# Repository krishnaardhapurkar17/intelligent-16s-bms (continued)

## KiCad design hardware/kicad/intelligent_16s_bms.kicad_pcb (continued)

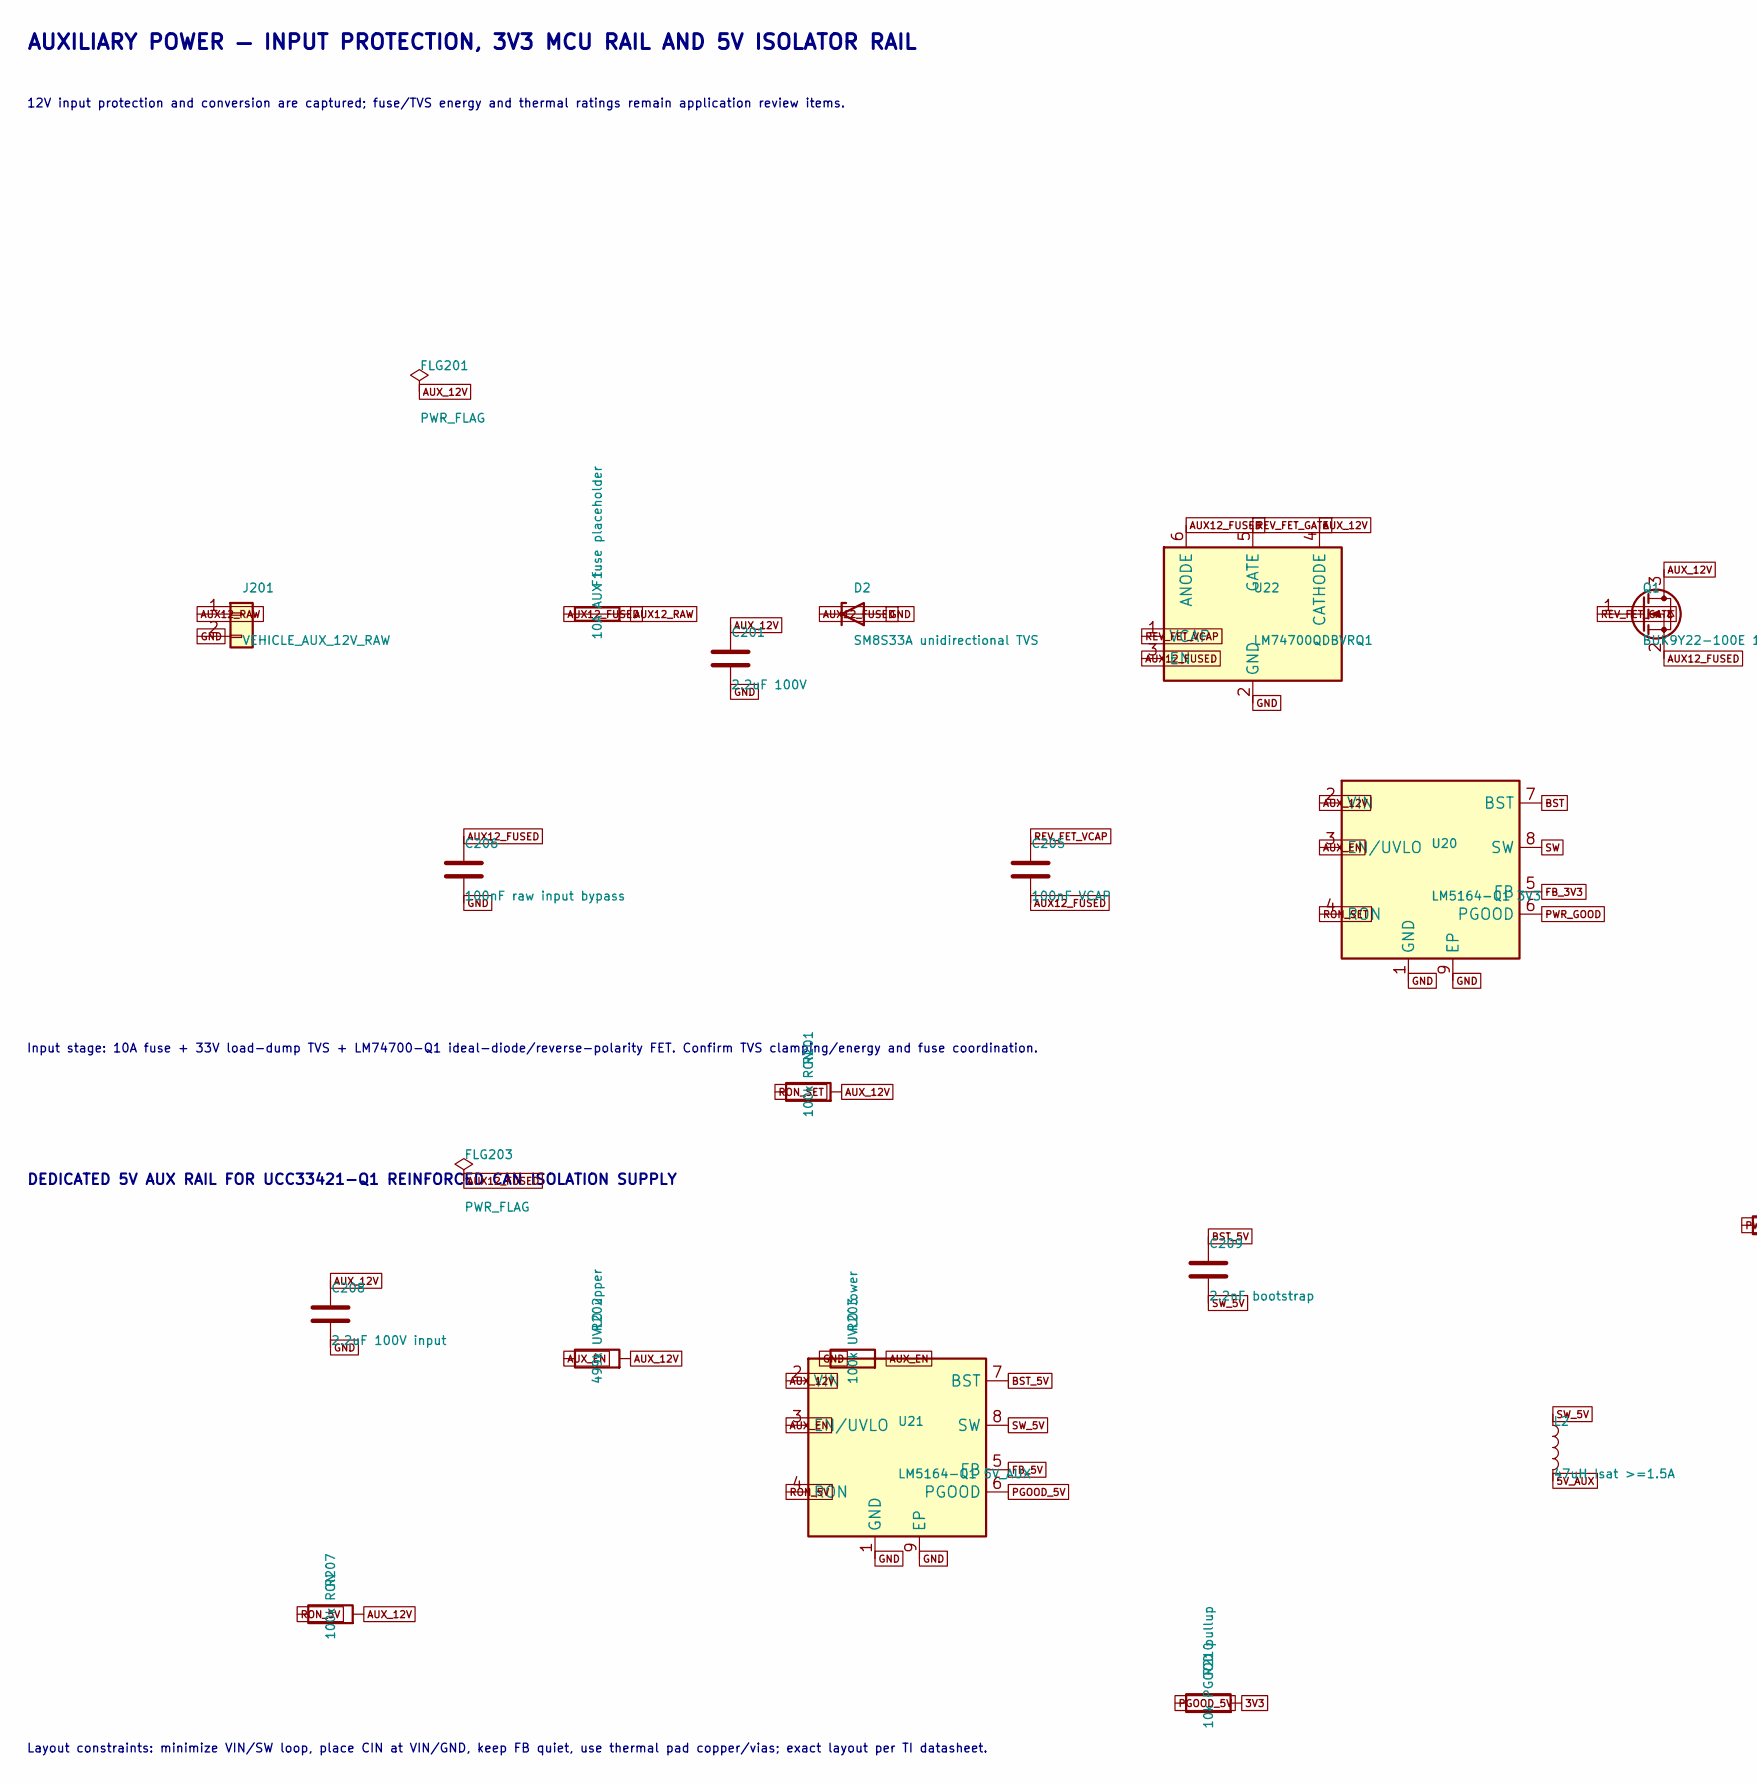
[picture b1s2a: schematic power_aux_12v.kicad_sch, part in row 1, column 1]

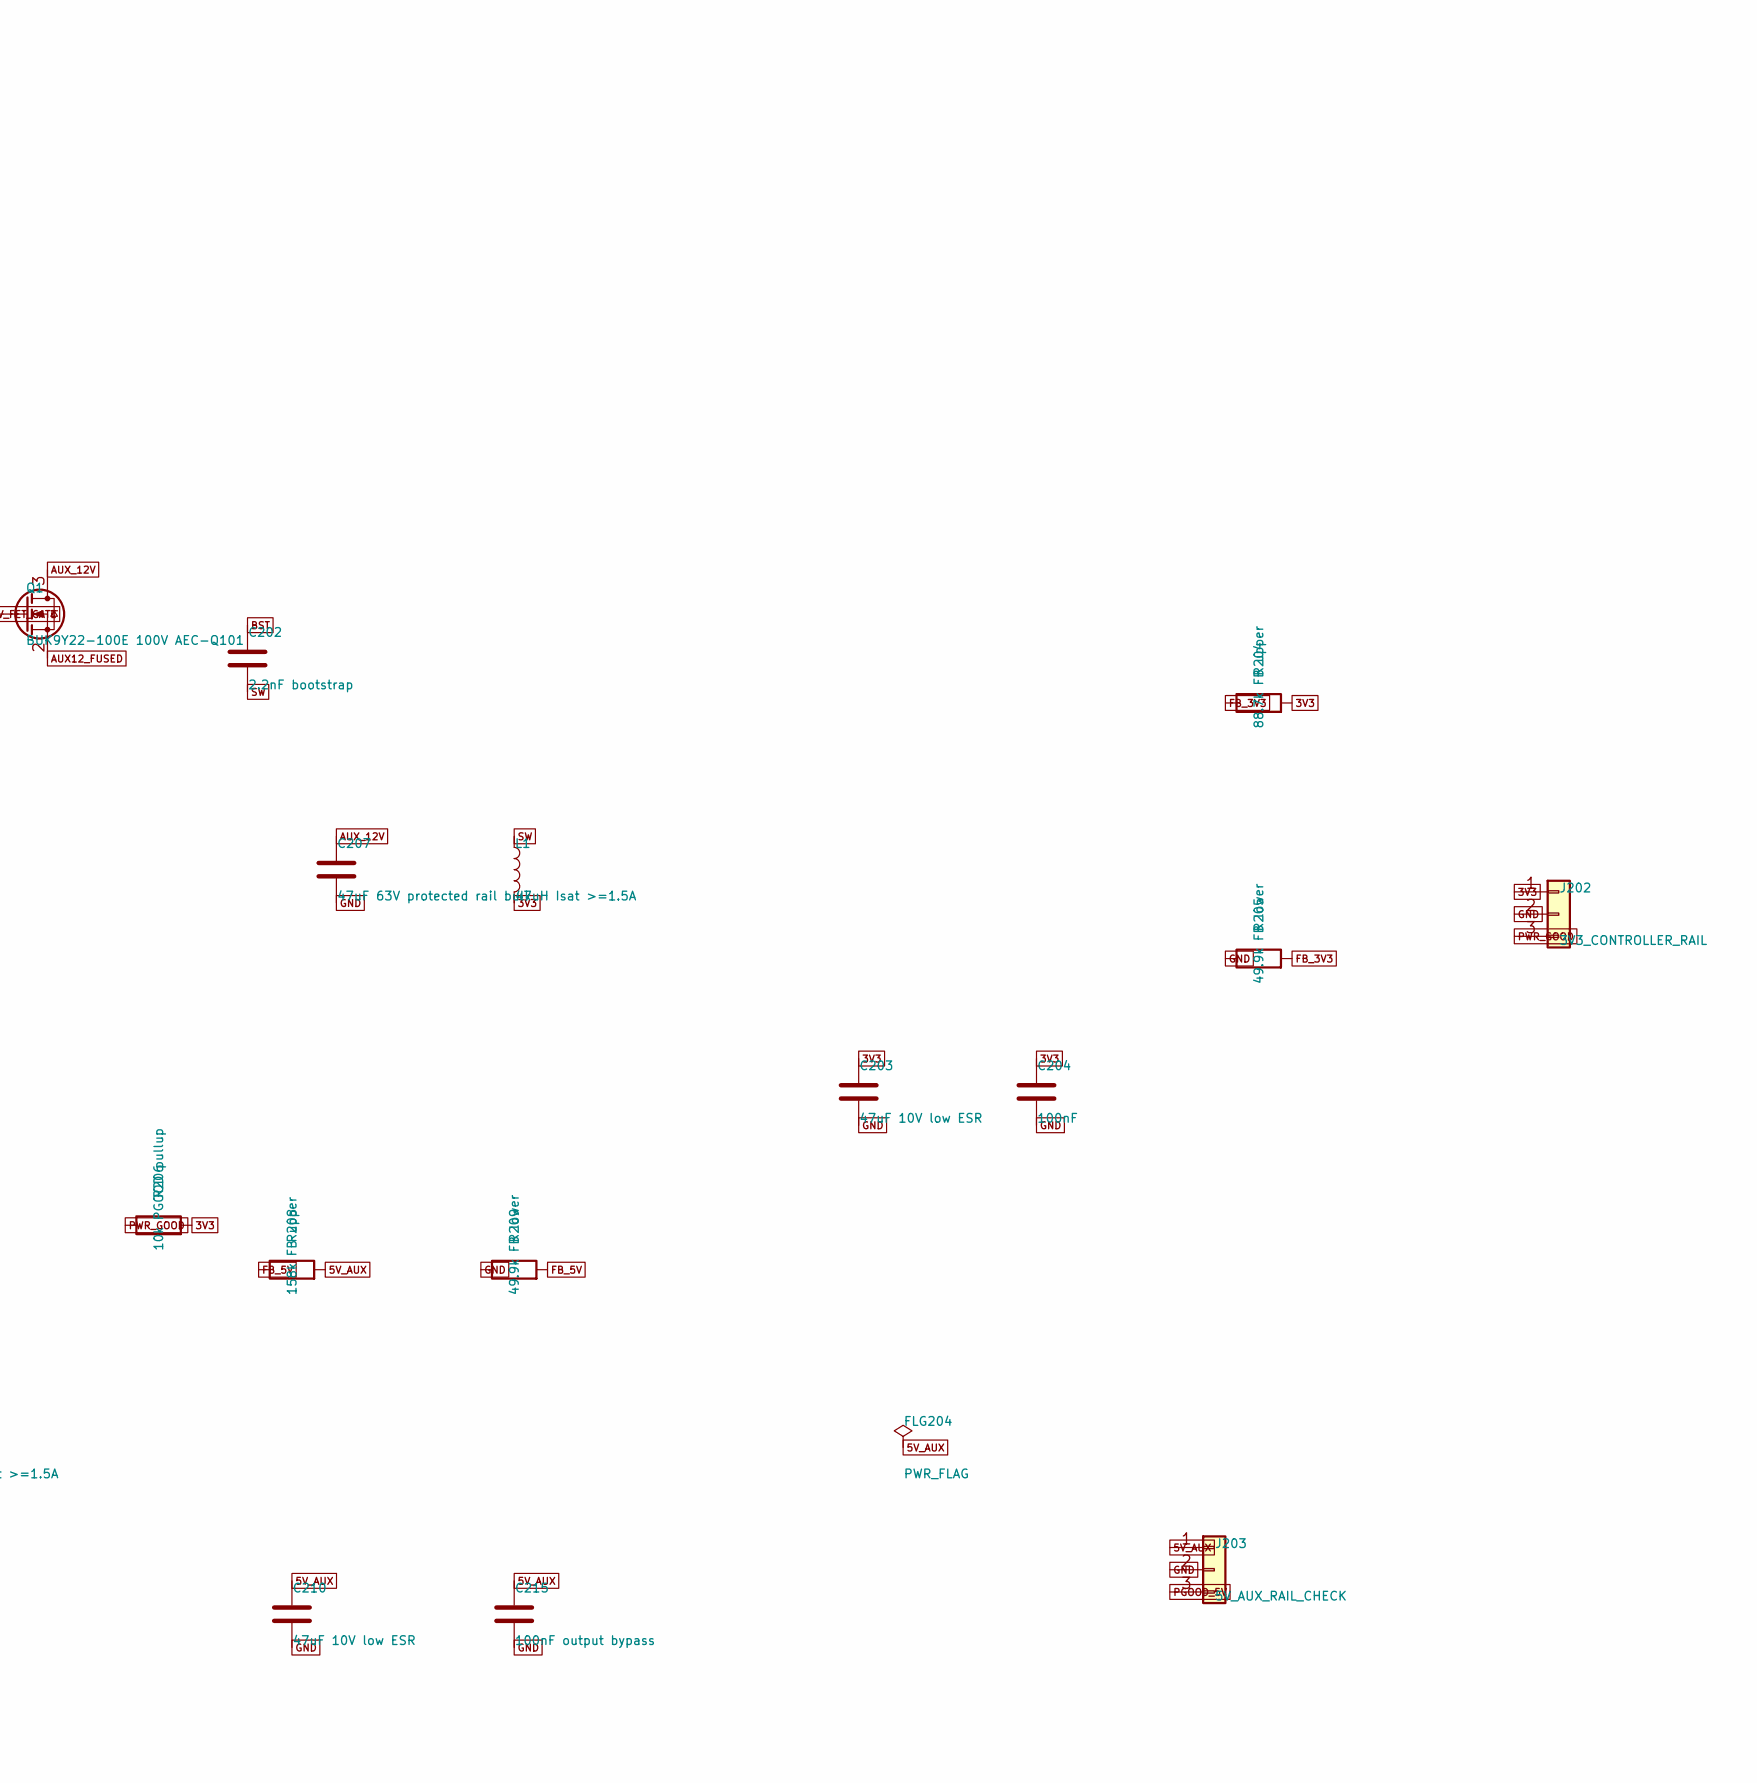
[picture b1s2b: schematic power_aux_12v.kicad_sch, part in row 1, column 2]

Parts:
C201: 2.2uF 100V; C_1210_3225Metric
C202, C209: 2.2nF bootstrap; C_0603_1608Metric
C203, C210: 47uF 10V low ESR; C_1210_3225Metric
C204: 100nF; C_0603_1608Metric
C205: 100nF VCAP; C_0603_1608Metric
C206: 100nF raw input bypass; C_0603_1608Metric
C207: 47uF 63V protected rail bulk; C_1210_3225Metric
C208: 2.2uF 100V input; C_1210_3225Metric
C215: 100nF output bypass; C_0603_1608Metric
D2: SM8S33A unidirectional TVS
F1: 10A AUX fuse placeholder
FLG201, FLG203, FLG204: PWR_FLAG
J201: VEHICLE_AUX_12V_RAW; TerminalBlock_Phoenix_MKDS-1,5-2-5.08_1x02_P5.08mm_Horizont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
J202: 3V3_CONTROLLER_RAIL; PinHeader_1x03_P2.54mm_Vertical
J203: 5V_AUX_RAIL_CHECK; PinHeader_1x03_P2.54mm_Vertical
L1, L2: 47uH Isat >=1.5A; L_12x12mm_H6mm
Q1: BUK9Y22-100E 100V AEC-Q101; LFPAK56
R201, R207: 100k RON; R_0603_1608Metric
R202: 499k UVLO upper; R_0603_1608Metric
R203: 100k UVLO lower; R_0603_1608Metric
R204: 88.7k FB upper; R_0603_1608Metric
R205, R209: 49.9k FB lower; R_0603_1608Metric
R206, R210: 10k PGOOD pullup; R_0603_1608Metric
R208: 158k FB upper; R_0603_1608Metric
U20: LM5164-Q1 3V3; TI_SO-PowerPAD-8
U21: LM5164-Q1 5V_AUX; TI_SO-PowerPAD-8
U22: LM74700QDBVRQ1; SOT-23-6

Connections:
3V3: C203.1, C204.1, J202.1, L1.2, R204.2, R206.2, R210.2; also elsewhere on the board
5V_AUX: C210.1, C215.1, FLG204.1, J203.1, L2.2, R208.2; also elsewhere on the board
AUX12_FUSED: C205.2, C206.1, D2.1 (K), F1.1, FLG203.1, Q1.2 (S), U22.3 (EN), U22.6 (ANODE)
AUX12_RAW: F1.2, J201.1
AUX_12V: C201.1, C207.1, C208.1, FLG201.1, Q1.3 (D), R201.2, R202.2, R207.2, U20.2 (VIN), U21.2 (VIN), U22.4 (CATHODE); also elsewhere on the board
AUX_EN: R202.1, R203.2, U20.3 (EN/UVLO), U21.3 (EN/UVLO)
BST: C202.1, U20.7 (BST)
BST_5V: C209.1, U21.7 (BST)
FB_3V3: R204.1, R205.2, U20.5 (FB)
FB_5V: R208.1, R209.2, U21.5 (FB)
GND: C201.2, C203.2, C204.2, C206.2, C207.2, C208.2, C210.2, C215.2, D2.2 (A), J201.2, J202.2, J203.2, R203.1, R205.1, R209.1, U20.1 (GND), U20.9 (EP), U21.1 (GND), U21.9 (EP), U22.2 (GND); also elsewhere on the board
PGOOD_5V: J203.3, R210.1, U21.6 (PGOOD)
PWR_GOOD: J202.3, R206.1, U20.6 (PGOOD)
REV_FET_GATE: Q1.1 (G), U22.5 (GATE)
REV_FET_VCAP: C205.1, U22.1 (VCAP)
RON_5V: R207.1, U21.4 (RON)
RON_SET: R201.1, U20.4 (RON)
SW: C202.2, L1.1, U20.8 (SW)
SW_5V: C209.2, L2.1, U21.8 (SW)

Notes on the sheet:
Layout constraints: minimize VIN/SW loop, place CIN at VIN/GND, keep FB quiet, use thermal pad copper/vias; exact layout per TI datasheet.
12V input protection and conversion are captured; fuse/TVS energy and thermal ratings remain application review items.
DEDICATED 5V AUX RAIL FOR UCC33421-Q1 REINFORCED CAN ISOLATION SUPPLY
AUXILIARY POWER — INPUT PROTECTION, 3V3 MCU RAIL AND 5V ISOLATOR RAIL
Input stage: 10A fuse + 33V load-dump TVS + LM74700-Q1 ideal-diode/reverse-polarity FET. Confirm TVS clamping/energy and fuse coordination.

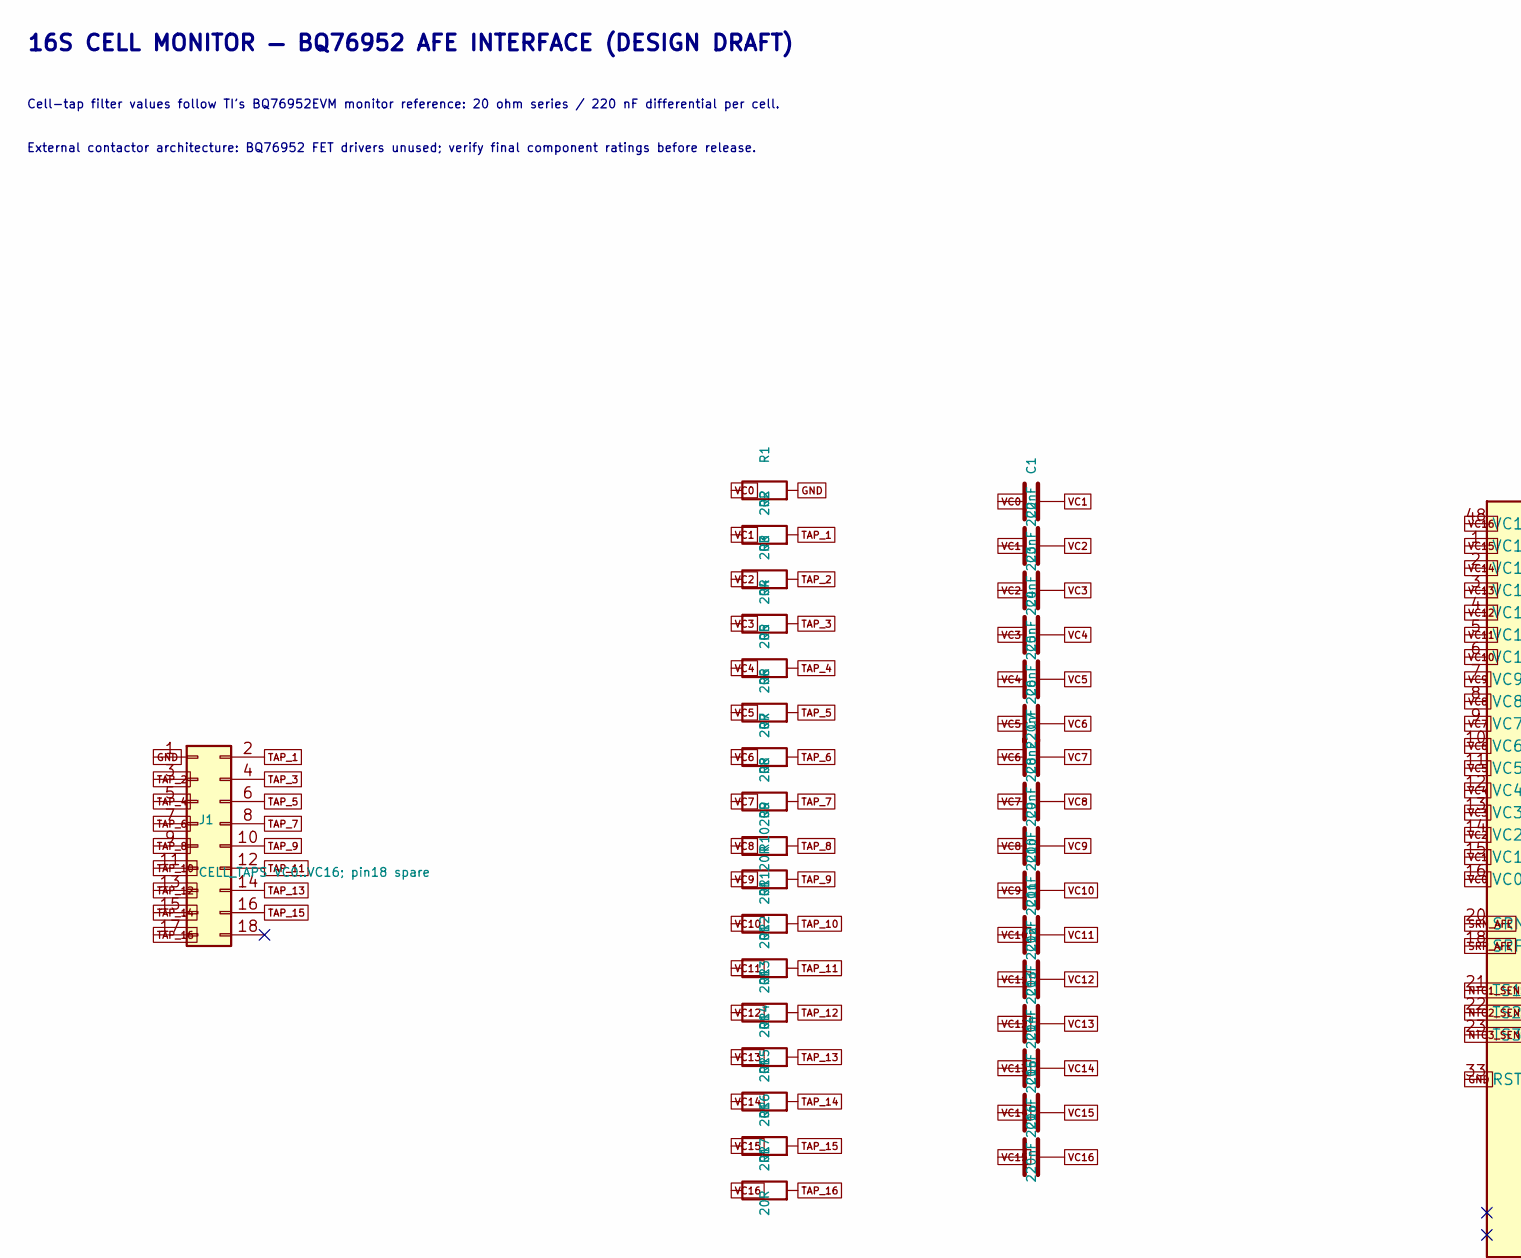
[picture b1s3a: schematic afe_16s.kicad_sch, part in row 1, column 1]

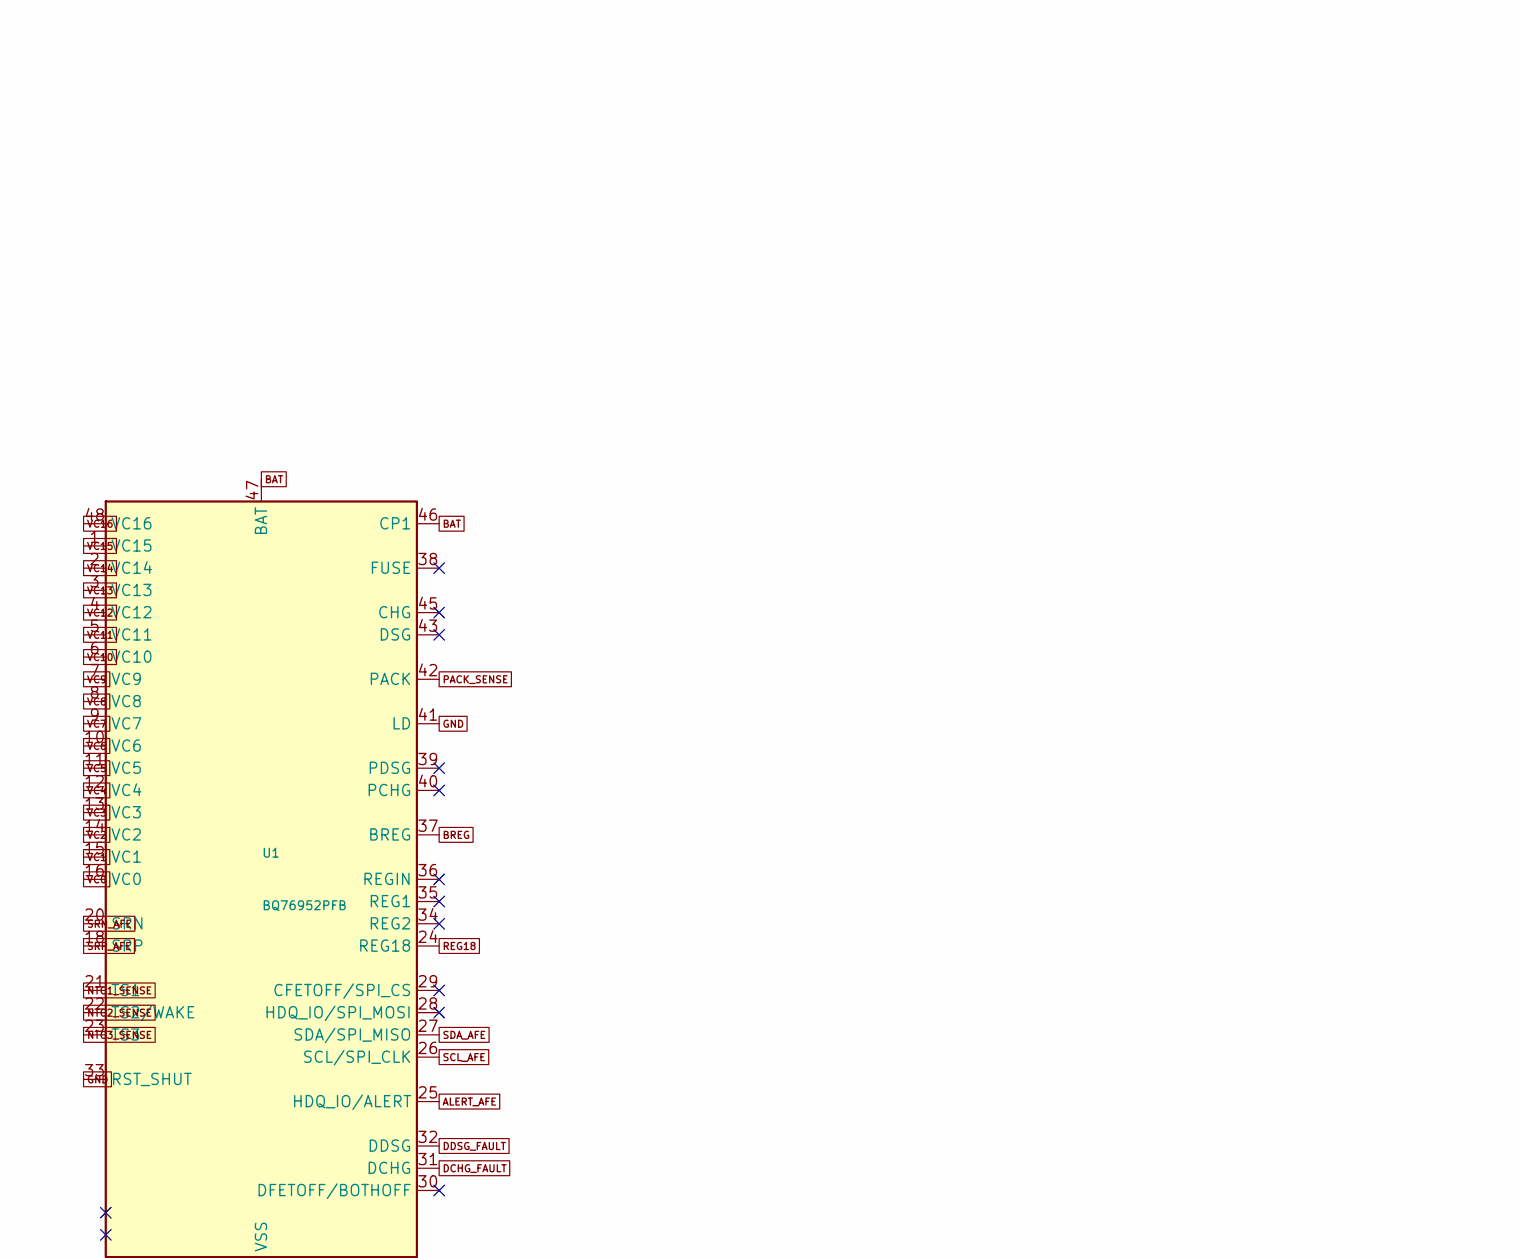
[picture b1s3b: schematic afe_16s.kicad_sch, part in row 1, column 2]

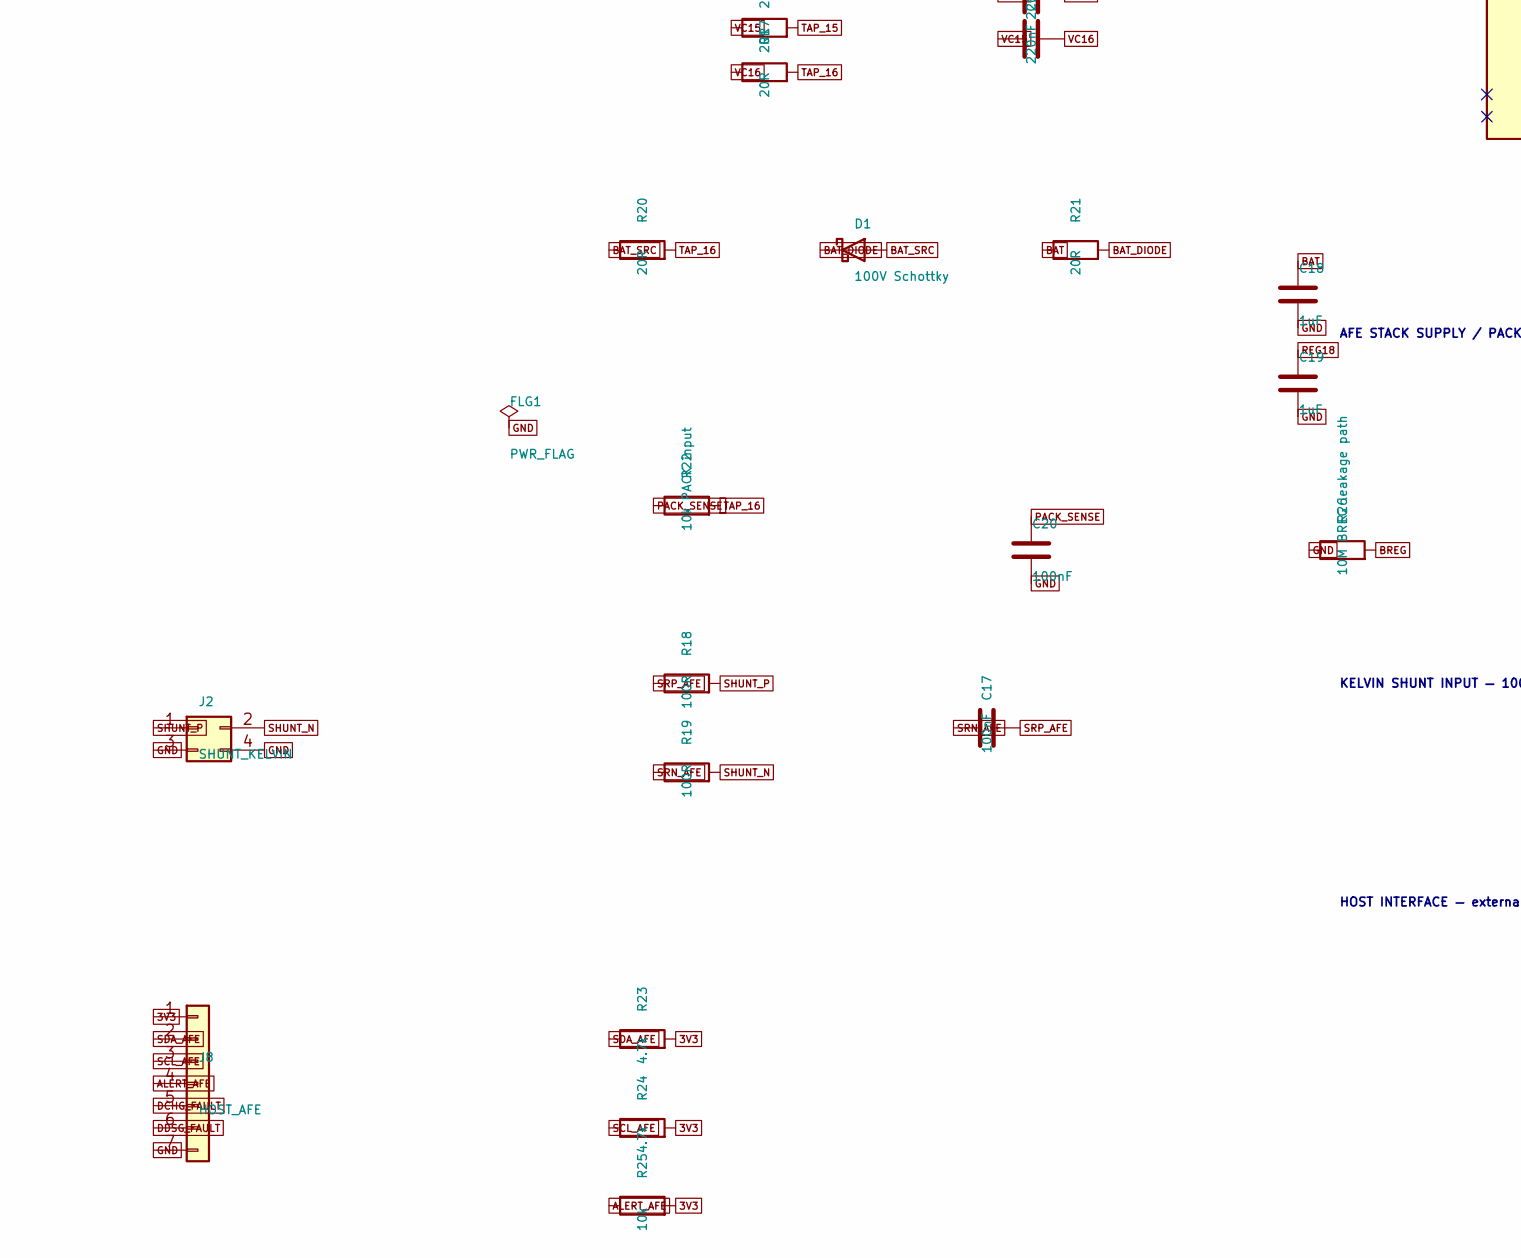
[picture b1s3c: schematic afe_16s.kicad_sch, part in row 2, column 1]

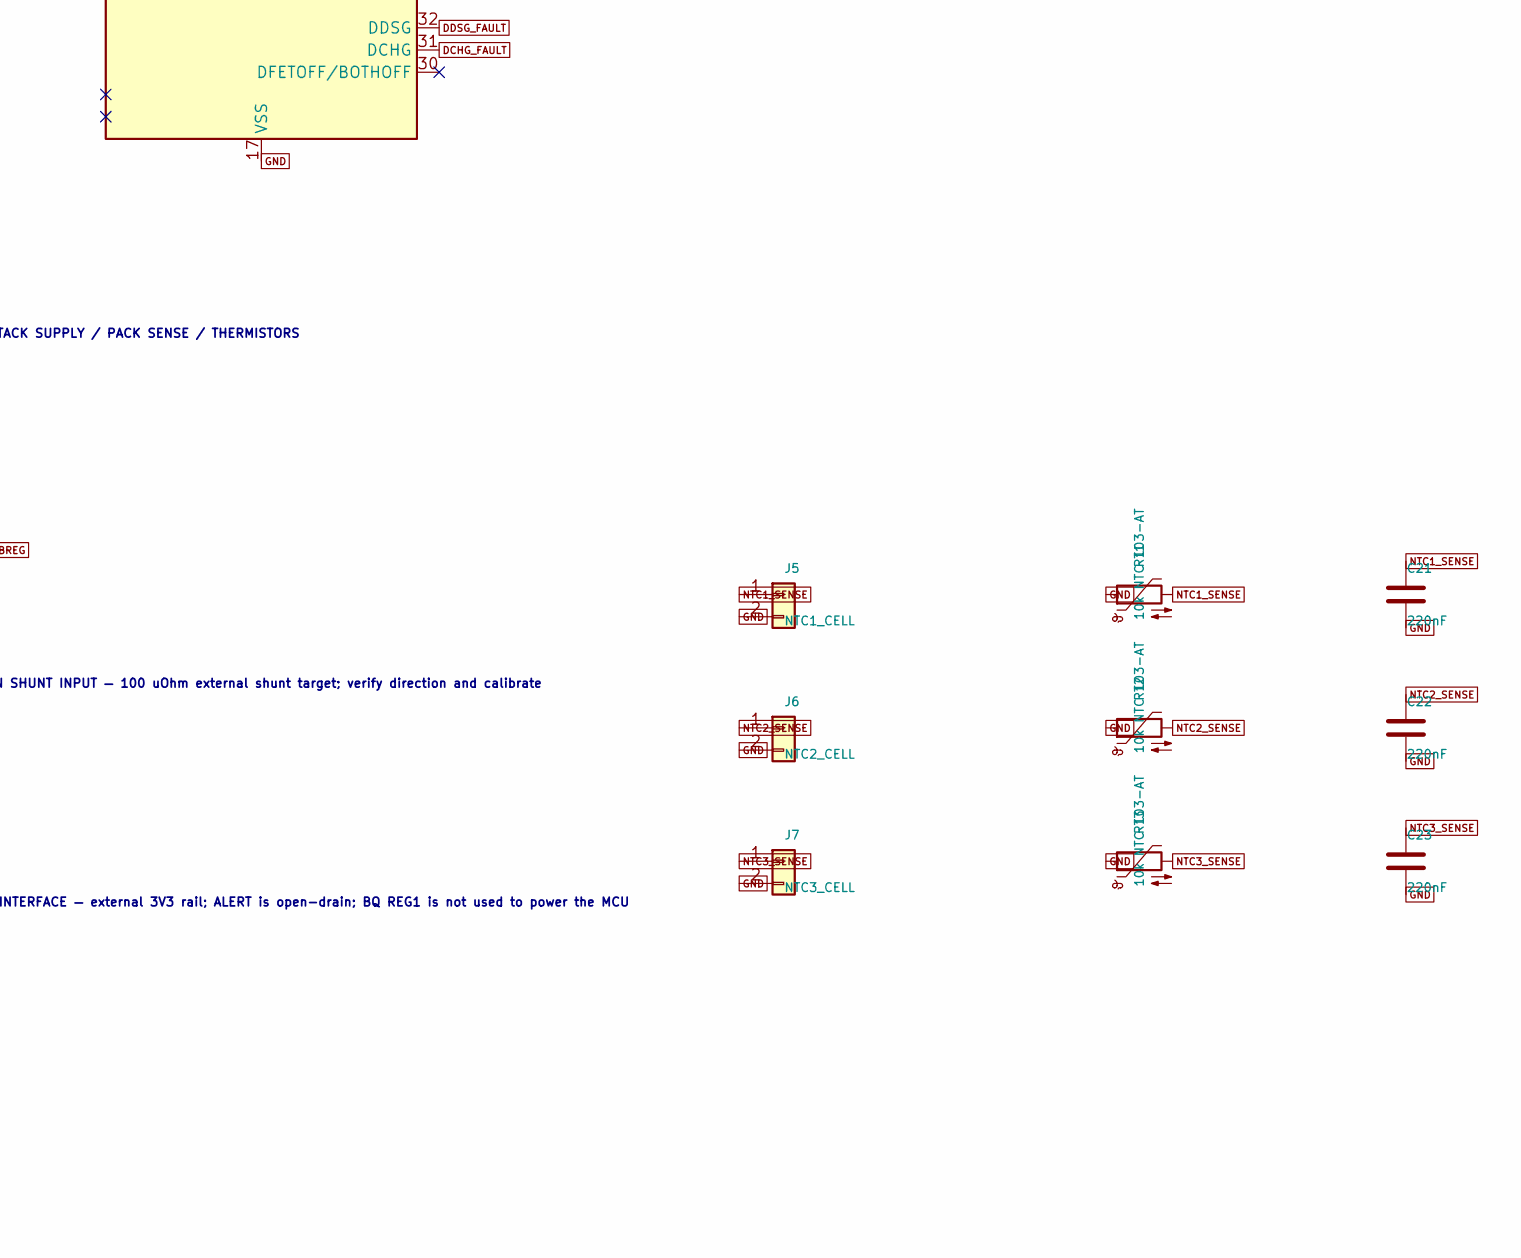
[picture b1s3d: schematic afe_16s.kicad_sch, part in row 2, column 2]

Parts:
C1, C2, C3, C4, C5, C6, C7, C8, C9, C10, C11, C12, C13, C14, C15, C16, C21, C22, C23: 220nF; C_0603_1608Metric
C17, C20: 100nF; C_0603_1608Metric
C18, C19: 1uF; C_0603_1608Metric
D1: 100V Schottky; D_SOD-123
FLG1: PWR_FLAG
J1: CELL_TAPS VC0..VC16; pin18 spare; Molex_Micro-Fit_3.0_43045-1818_2x09-1MP_P3.00mm_Vertical
J2: SHUNT_KELVIN; Molex_Micro-Fit_3.0_43045-0412_2x02_P3.00mm_Vertical
J5: NTC1_CELL; PinHeader_1x02_P2.54mm_Vertical
J6: NTC2_CELL; PinHeader_1x02_P2.54mm_Vertical
J7: NTC3_CELL; PinHeader_1x02_P2.54mm_Vertical
J8: HOST_AFE; PinHeader_1x07_P2.54mm_Vertical
R1, R2, R3, R4, R5, R6, R7, R8, R9, R10, R11, R12, R13, R14, R15, R16, R17, R20, R21: 20R; R_0603_1608Metric
R18, R19: 100R; R_0603_1608Metric
R22: 10k PACK input; R_0603_1608Metric
R23, R24: 4.7k; R_0603_1608Metric
R25: 10k; R_0603_1608Metric
R26: 10M BREG leakage path; R_0603_1608Metric
RT1, RT2, RT3: 10k NTC 103-AT; R_0603_1608Metric
U1: BQ76952PFB; TQFP-48_7x7mm_P0.5mm

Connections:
3V3: J8.1, R23.2, R24.2, R25.2; also elsewhere on the board
ALERT_AFE: J8.4, R25.1, U1.25 (HDQ_IO/ALERT); also elsewhere on the board
BAT: C18.1, R21.1, U1.46 (CP1), U1.47 (BAT)
BAT_DIODE: D1.1 (K), R21.2
BAT_SRC: D1.2 (A), R20.1
BREG: R26.2, U1.37 (BREG)
DCHG_FAULT: J8.5, U1.31 (DCHG)
DDSG_FAULT: J8.6, U1.32 (DDSG)
GND: C18.2, C19.2, C20.2, C21.2, C22.2, C23.2, FLG1.1, J1.1, J2.3, J2.4, J5.2, J6.2, J7.2, J8.7, R1.2, R26.1, RT1.1, RT2.1, RT3.1, U1.17 (VSS), U1.33 (RST_SHUT), U1.41 (LD); also elsewhere on the board
NTC1_SENSE: C21.1, J5.1, RT1.2, U1.21 (TS1)
NTC2_SENSE: C22.1, J6.1, RT2.2, U1.22 (TS2/WAKE)
NTC3_SENSE: C23.1, J7.1, RT3.2, U1.23 (TS3)
PACK_SENSE: C20.1, R22.1, U1.42 (PACK)
REG18: C19.1, U1.24 (REG18); also elsewhere on the board
SCL_AFE: J8.3, R24.1, U1.26 (SCL/SPI_CLK); also elsewhere on the board
SDA_AFE: J8.2, R23.1, U1.27 (SDA/SPI_MISO); also elsewhere on the board
SHUNT_N: J2.2, R19.2
SHUNT_P: J2.1, R18.2
SRN_AFE: C17.1, R19.1, U1.20 (SRN)
SRP_AFE: C17.2, R18.1, U1.18 (SRP)
TAP_1: J1.2, R2.2
TAP_2: J1.3, R3.2
TAP_3: J1.4, R4.2
TAP_4: J1.5, R5.2
TAP_5: J1.6, R6.2
TAP_6: J1.7, R7.2
TAP_7: J1.8, R8.2
TAP_8: J1.9, R9.2
TAP_9: J1.10, R10.2
TAP_10: J1.11, R11.2
TAP_11: J1.12, R12.2
TAP_12: J1.13, R13.2
TAP_13: J1.14, R14.2
TAP_14: J1.15, R15.2
TAP_15: J1.16, R16.2
TAP_16: J1.17, R17.2, R20.2, R22.2
VC0: C1.1, R1.1, U1.16 (VC0)
VC1: C1.2, C2.1, R2.1, U1.15 (VC1)
VC2: C2.2, C3.1, R3.1, U1.14 (VC2)
VC3: C3.2, C4.1, R4.1, U1.13 (VC3)
VC4: C4.2, C5.1, R5.1, U1.12 (VC4)
VC5: C5.2, C6.1, R6.1, U1.11 (VC5)
VC6: C6.2, C7.1, R7.1, U1.10 (VC6)
VC7: C7.2, C8.1, R8.1, U1.9 (VC7)
VC8: C8.2, C9.1, R9.1, U1.8 (VC8)
VC9: C9.2, C10.1, R10.1, U1.7 (VC9)
VC10: C10.2, C11.1, R11.1, U1.6 (VC10)
VC11: C11.2, C12.1, R12.1, U1.5 (VC11)
VC12: C12.2, C13.1, R13.1, U1.4 (VC12)
VC13: C13.2, C14.1, R14.1, U1.3 (VC13)
VC14: C14.2, C15.1, R15.1, U1.2 (VC14)
VC15: C15.2, C16.1, R16.1, U1.1 (VC15)
VC16: C16.2, R17.1, U1.48 (VC16)

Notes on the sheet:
16S CELL MONITOR — BQ76952 AFE INTERFACE (DESIGN DRAFT)
KELVIN SHUNT INPUT — 100 uOhm external shunt target; verify direction and calibrate
HOST INTERFACE — external 3V3 rail; ALERT is open-drain; BQ REG1 is not used to power the MCU
External contactor architecture: BQ76952 FET drivers unused; verify final component ratings before release.
AFE STACK SUPPLY / PACK SENSE / THERMISTORS
Cell-tap filter values follow TI's BQ76952EVM monitor reference: 20 ohm series / 220 nF differential per cell.

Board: 2 copper layers, 294 parts (0 on the bottom side), 257 nets, no tracks yet.

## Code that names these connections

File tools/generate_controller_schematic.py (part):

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    s.add_symbol("Connector_Generic:Conn_01x03", "J1", "3V3_VSS_IN", 55, 85,
                 "Connector_PinHeader_2.54mm:PinHeader_1x03_P2.54mm_Vertical",
                 nets={"1":"3V3", "2":"GND", "3":"MCU_EN"})
    s.add_symbol("Device:R", "R1", "10k MCU_EN pullup", 90, 85, "Resistor_SMD:R_0603_1608Metric", angle=90,
                 nets={"1":"3V3", "2":"MCU_EN"})
    s.add_symbol("Device:R", "R10", "10k IO0 strap pullup", 90, 95, "Resistor_SMD:R_0603_1608Metric", angle=90,
                 nets={"1":"3V3", "2":"IO0_BOOT"})
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    s.add_symbol("Device:R", "R43", "10k watchdog rearm default-high", 520, 350,
                 "Resistor_SMD:R_0603_1608Metric", angle=90,
                 nets={"1":"3V3", "2":"WD_REARM_N"})
    s.text("TPS3430 WDO pulse and startup power fault set a cross-coupled NAND latch. GPIO42 must pulse WD_REARM_N low only after a healthy heartbeat; default is latched-off.", 30, 450)
    s.text("LTC3300 WDT status is diode-ORed to GPIO41; BMS_PERMIT is isolated to each balancer and forces its local WDT high on a hardware inhibit.", 30, 457)
    for i, status in enumerate(("BAL_WDT30", "BAL_WDT31", "BAL_WDT32")):
        s.add_symbol("Device:D_Schottky", f"D{8+i}", "BAT54H-Q WDT status OR", 560, 335 + i*10,
                     "Diode_SMD:D_SOD-123",
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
